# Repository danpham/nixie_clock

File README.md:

# Nixie Clock ESP32-C3

A **Nixie tube clock project** based on the **ESP32-C3**, using **IN14** and **IN3** tubes driven by **HV5622** high-voltage drivers.

## Hardware

- **Microcontroller:** ESP32-C3  
- **Nixie tubes:** 6 × IN14 and 2 × IN3  
- **Driver:** HV5622 for cathode switching  
- **Rotary encoder:** EC11 for time configuration  
- **3.3V regulator:** AP63203WU to power the ESP32-C3 and logic components  
- **PCB design:** SMD (Surface-Mount) components

> [!WARNING]
> This project involves high voltage. Follow proper electrical safety procedures!

## Current Features

- Nixie tube display control via HV5622
- Rotary encoder input (EC11) for setting the time
- Internal clock management
- **Anti–cathode poisoning routine:** periodic cycling and cathode management to prevent oxide buildup and extend tube lifespan
- Wi-Fi connectivity with NTP time synchronization
- Web interface for configuration

## Future Features

- Web interface for configuration: timezone, brightness, night mode, and display enable/disable

## Software

The code is written in **C for the ESP32-C3**, organized as follows:

```
software/nixie_clock_esp32_project/
├── components/
│   ├── uart/
│   ├── gpio_driver/
│   ├── display/
│   ├── clock/
│   ├── hv5622/
│   ├── rotary_encoder/
│   └── wifi/
└── main/
```

### Code Quality & Standards

- The firmware is developed in compliance with MISRA C:2012 guidelines to ensure reliability and safety in embedded systems.
- Modular driver-based architecture for maintainability and scalability.

## Usage

### Wi-Fi Configuration

To connect to the Nixie clock, use the following credentials:

```c
WIFI_SSID     "NixieClock-Setup"
WIFI_PASSWORD "12345678"
```

### Compilation

The project uses **ESP-IDF for ESP32-C3**. Make sure your ESP32-C3 development environment is properly set up.

```bash
cd software/nixie_clock_esp32_project
idf.py build
idf.py flash
```

## Test

### Unit testing

In ESP-IDF terminal:
```bash
cd software/nixie_clock_esp32_project/test/unit
cmake -S . -B build
cmake --build build --config Release
.\build\Release\native_tests.exe
```

### Integration testing

In ESP-IDF terminal:
```bash
cd software/nixie_clock_esp32_project/test/integration
cmake -S . -B build
cmake --build build --config Release
.\build\Release\native_integration_tests.exe
```

## Documentation

The generated documentation for this project is available [here](https://danpham.github.io/nixie_clock/).

## License

This project is released under the **LGPL v3** license.
A separate `LICENSE` file contains the complete text of the license.

## Safety

> [!WARNING]
> This project involves **high voltage (~170V for Nixie tubes)**.

- Never touch the circuit while it is powered
- Work carefully and only with proper knowledge of high-voltage electronics

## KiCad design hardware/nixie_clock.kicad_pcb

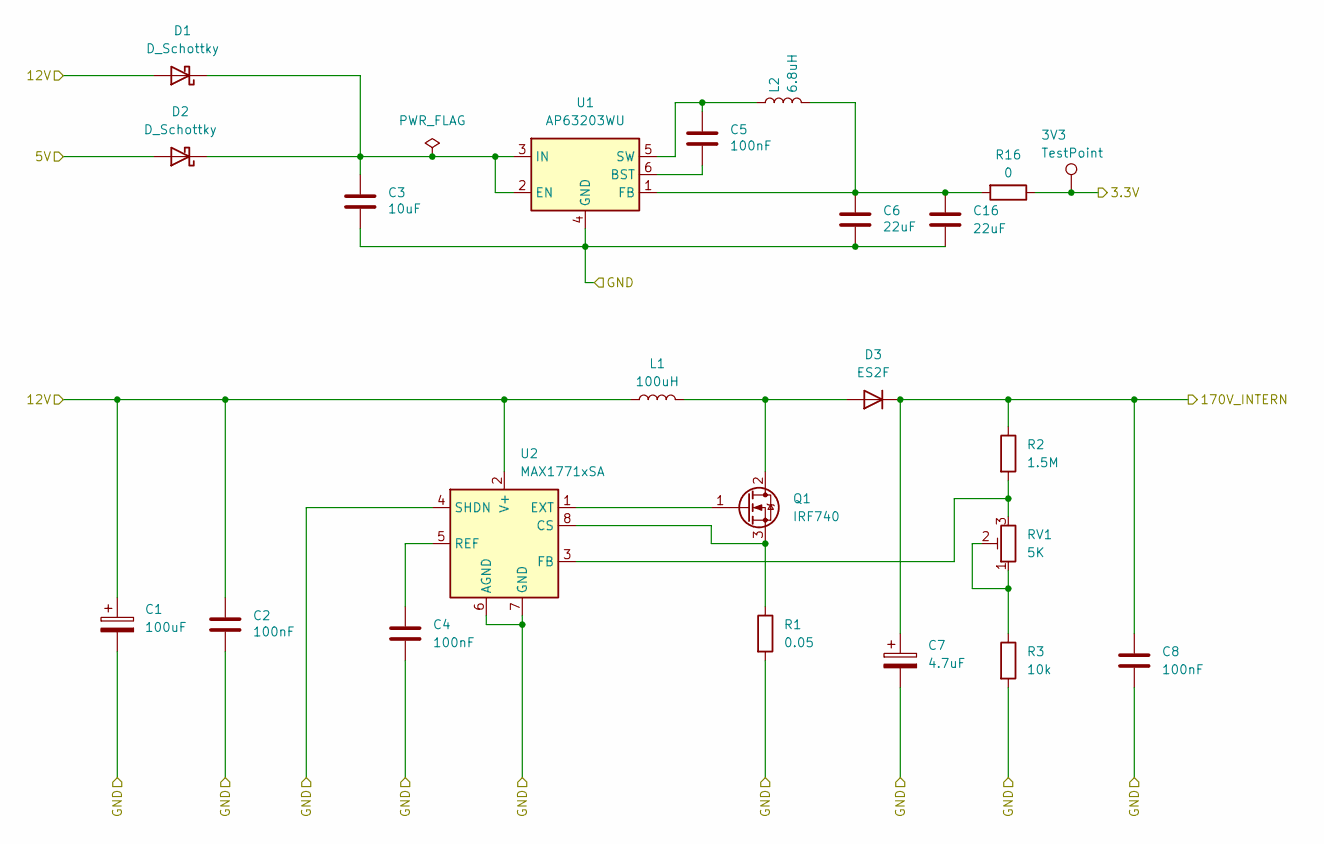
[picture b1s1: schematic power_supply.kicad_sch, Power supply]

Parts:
3V3: TestPoint; TestPoint_Pad_D1.5mm
C1: 100uF; CP_EIA-7343-31_Kemet-D_HandSolder
C2, C4, C5: 100nF; C_0805_2012Metric
C3: 10uF; C_1206_3216Metric
C6, C16: 22uF; C_1206_3216Metric
C7: 4.7uF; C_Elec_8x10.2
C8: 100nF; C_1210_3225Metric_Pad1.33x2.70mm_HandSolder
D1, D2: D_Schottky; D_SMB
D3: ES2F; D_SMB
L1: 100uH; L_APV_APH1050
L2: 6.8uH; L_Bourns_SRN8040TA
Q1: IRF740; TO-263-2
R1: 0.05; R_0805_2012Metric
R2: 1.5M; R_0805_2012Metric
R3: 10k; R_0805_2012Metric
R16: 0; R_1206_3216Metric
RV1: 5K; Potentiometer_Bourns_3314J_Vertical
U1: AP63203WU; TSOT-23-6
U2: MAX1771xSA; SO-8_3.9x4.9mm_P1.27mm

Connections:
/connectors/5V: D2.2 (A); also elsewhere on the board
/connectors/12V: C1.1, C2.1, D1.2 (A), L1.1, U2.2 (V+); also elsewhere on the board
/connectors/GND: C1.2, C2.2, C3.2, C4.2, C6.2, C7.2, C8.2, C16.2, R1.2, R3.2, U1.4 (GND), U2.4 (SHDN), U2.6 (AGND), U2.7 (GND); also elsewhere on the board
/cpu/3.3V: 3V3.1, R16.1; also elsewhere on the board
/driver_3_digits_1_dot_left/170V_INTERN: C7.1, C8.1, D3.1 (K), R2.1; also elsewhere on the board
unnamed: C3.1, D1.1 (K), D2.1 (K), U1.2 (EN), U1.3 (IN)
unnamed: D3.2 (A), L1.2, Q1.2 (D)
unnamed: Q1.1 (G), U2.1 (EXT)
unnamed: Q1.3 (S), R1.1, U2.8 (CS)
unnamed: R3.1, RV1.1, RV1.2
unnamed: C5.2, U1.6 (BST)
unnamed: C6.1, C16.1, L2.2, R16.2, U1.1 (FB)
unnamed: C5.1, L2.1, U1.5 (SW)
unnamed: R2.2, RV1.3, U2.3 (FB)
unnamed: C4.1, U2.5 (REF)

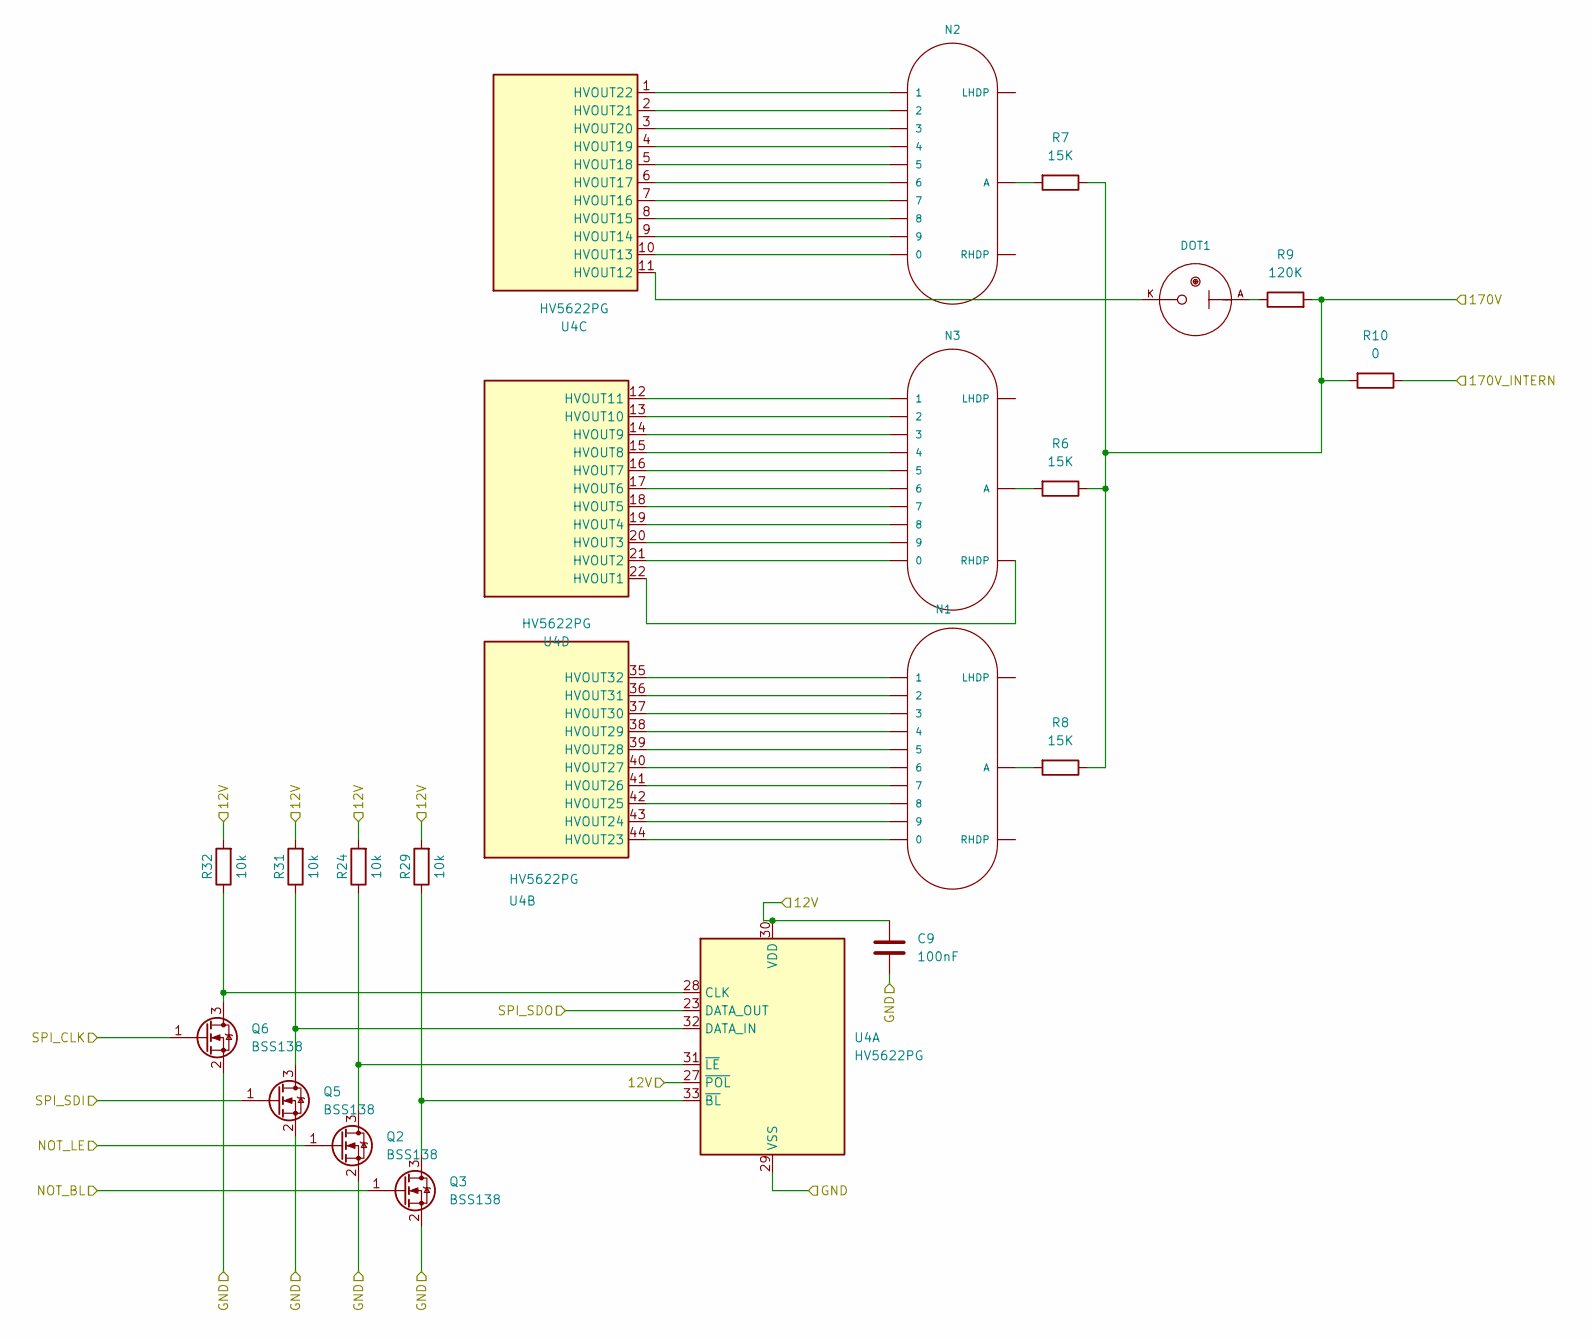
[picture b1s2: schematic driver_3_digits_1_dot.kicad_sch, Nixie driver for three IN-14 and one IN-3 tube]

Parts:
C9: 100nF; R_0805_2012Metric
DOT1: IN-3; nixies-us-IN-3
N1, N2, N3: IN-14; nixies-us-IN-14
Q2, Q3, Q5, Q6: BSS138; SOT-23
R6, R7, R8: 15K; R_1206_3216Metric
R9: 120K; R_1206_3216Metric
R10: 0; R_1206_3216Metric
R24, R29, R31, R32: 10k; R_0805_2012Metric
U4: HV5622PG; PQFP-44_10x10mm_P0.8mm

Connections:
/connectors/12V: C9.2, R24.2, R29.2, R31.2, R32.2, U4.27 (~POL), U4.30 (VDD); also elsewhere on the board
/connectors/170V: R6.1, R7.1, R8.1, R9.2, R10.2; also elsewhere on the board
/connectors/GND: C9.1, Q2.2 (S), Q3.2 (S), Q5.2 (S), Q6.2 (S), U4.29 (VSS); also elsewhere on the board
/cpu/GPIO1: Q3.1 (G); also elsewhere on the board
/cpu/GPIO2: Q2.1 (G); also elsewhere on the board
/cpu/SPI_CLK: Q6.1 (G); also elsewhere on the board
/cpu/SPI_MOSI: Q5.1 (G); also elsewhere on the board
/driver_3_digits_1_dot_left/170V_INTERN: R10.1; also elsewhere on the board
/driver_3_digits_1_dot_left/SPI_SDO: U4.23 (DATA_OUT); also elsewhere on the board
unnamed: DOT1.A, R9.1
unnamed: N1.A, R8.2
unnamed: N2.A, R7.2
unnamed: N3.A, R6.2
unnamed: Q2.3 (D), R24.1, U4.31 (~LE)
unnamed: Q3.3 (D), R29.1, U4.33 (~BL)
unnamed: Q5.3 (D), R31.1, U4.32 (DATA_IN)
unnamed: Q6.3 (D), R32.1, U4.28 (CLK)
unnamed: N1.0, U4.44 (HVOUT23)
unnamed: N1.9, U4.43 (HVOUT24)
unnamed: N1.8, U4.42 (HVOUT25)
unnamed: N1.7, U4.41 (HVOUT26)
unnamed: N1.6, U4.40 (HVOUT27)
unnamed: N1.5, U4.39 (HVOUT28)
unnamed: N1.4, U4.38 (HVOUT29)
unnamed: N1.3, U4.37 (HVOUT30)
unnamed: N1.2, U4.36 (HVOUT31)
unnamed: N1.1, U4.35 (HVOUT32)
unnamed: DOT1.K, U4.11 (HVOUT12)
unnamed: N2.0, U4.10 (HVOUT13)
unnamed: N2.9, U4.9 (HVOUT14)
unnamed: N2.8, U4.8 (HVOUT15)
unnamed: N2.7, U4.7 (HVOUT16)
unnamed: N2.6, U4.6 (HVOUT17)
unnamed: N2.5, U4.5 (HVOUT18)
unnamed: N2.4, U4.4 (HVOUT19)
unnamed: N2.3, U4.3 (HVOUT20)
unnamed: N2.2, U4.2 (HVOUT21)
unnamed: N2.1, U4.1 (HVOUT22)
unnamed: N3.RHDP, U4.22 (HVOUT1)
unnamed: N3.0, U4.21 (HVOUT2)
unnamed: N3.9, U4.20 (HVOUT3)
unnamed: N3.8, U4.19 (HVOUT4)
unnamed: N3.7, U4.18 (HVOUT5)
unnamed: N3.6, U4.17 (HVOUT6)
unnamed: N3.5, U4.16 (HVOUT7)
unnamed: N3.4, U4.15 (HVOUT8)
unnamed: N3.3, U4.14 (HVOUT9)
unnamed: N3.2, U4.13 (HVOUT10)
unnamed: N3.1, U4.12 (HVOUT11)

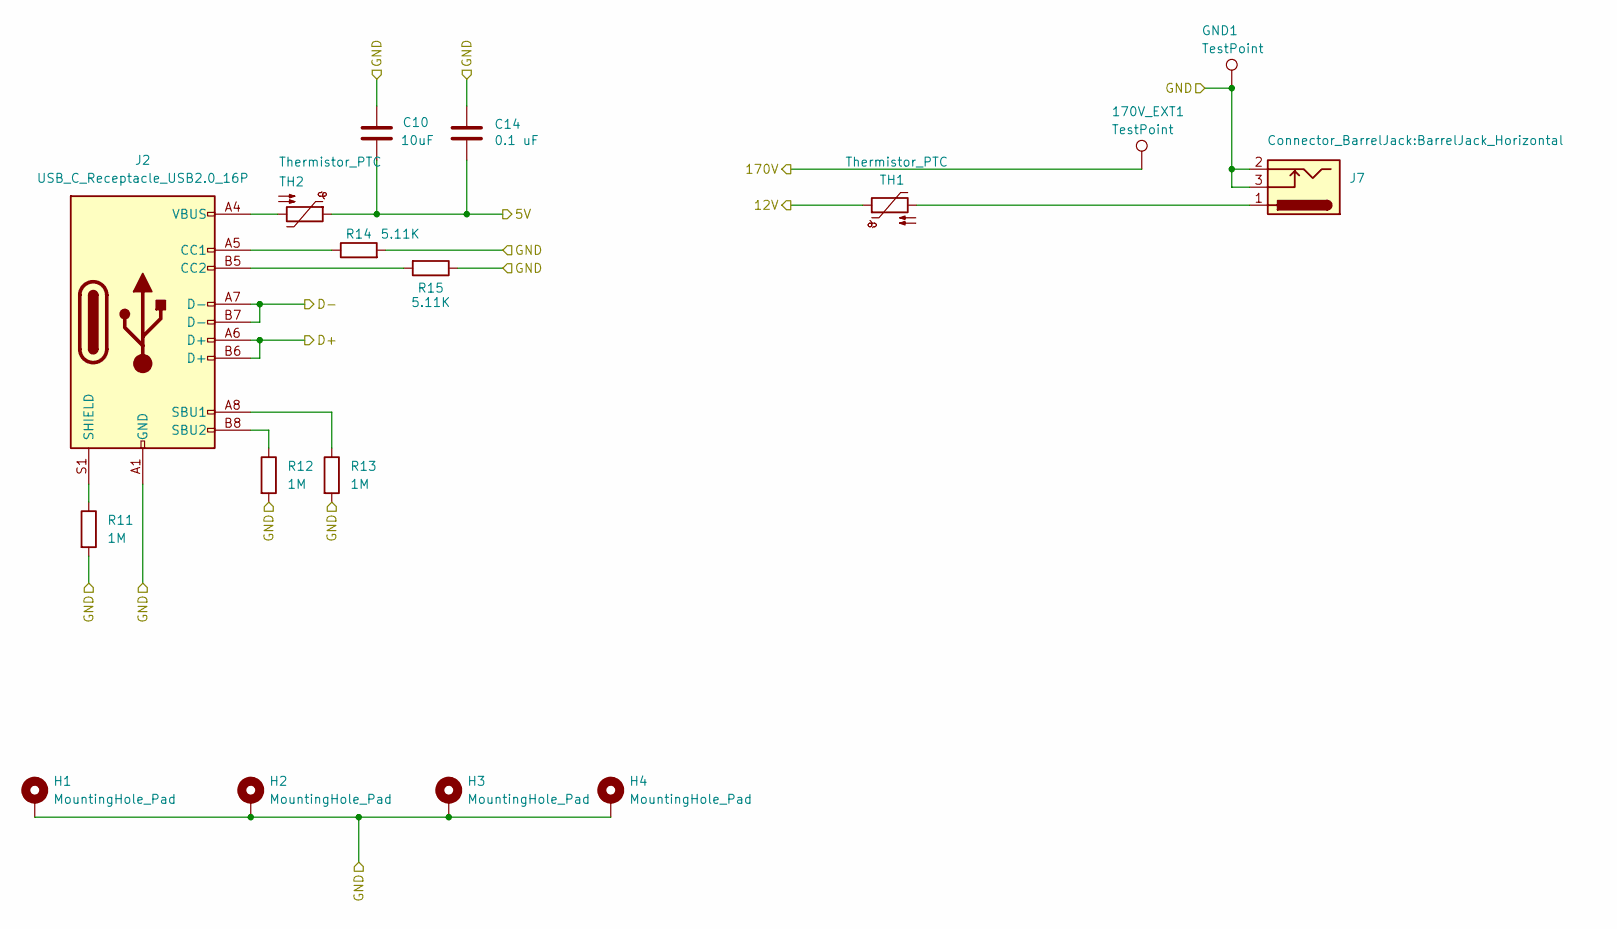
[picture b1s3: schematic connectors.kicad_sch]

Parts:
170V_EXT1: TestPoint; TestPoint_Pad_D1.5mm
C10: 10uF; C_1206_3216Metric
C14: 0.1 uF; C_0805_2012Metric
GND1: TestPoint; TestPoint_Pad_D1.5mm
H1, H2, H3, H4: MountingHole_Pad; MountingHole_3.2mm_M3_Pad_Via
J2: USB_C_Receptacle_USB2.0_16P; USB_C_Receptacle_GCT_USB4105-xx-A_16P_TopMnt_Horizontal
J7: Barrel_Jack_Switch; BarrelJack_Horizontal
R11, R12, R13: 1M; R_1206_3216Metric
R14, R15: 5.11K; R_1206_3216Metric
TH1, TH2: Thermistor_PTC; R_1206_3216Metric

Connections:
/connectors/5V: C10.2, C14.2, TH2.1; also elsewhere on the board
/connectors/12V: TH1.1; also elsewhere on the board
/connectors/170V: 170V_EXT1.1; also elsewhere on the board
/connectors/D+: J2.A6 (D+), J2.B6 (D+); also elsewhere on the board
/connectors/D-: J2.A7 (D-), J2.B7 (D-); also elsewhere on the board
/connectors/GND: C10.1, C14.1, GND1.1, H1.1, H2.1, H3.1, H4.1, J2.A1 (GND), J2.A12 (GND), J2.B1 (GND), J2.B12 (GND), J7.2, J7.3, R11.2, R12.2, R13.2, R14.2, R15.1; also elsewhere on the board
unnamed: J2.A5 (CC1), R14.1
unnamed: J2.B5 (CC2), R15.2
unnamed: J2.A8 (SBU1), R13.1
unnamed: J2.B8 (SBU2), R12.1
unnamed: J2.S1 (SHIELD), R11.1
unnamed: J2.A4 (VBUS), J2.A9 (VBUS), J2.B4 (VBUS), J2.B9 (VBUS), TH2.2
unnamed: J7.1, TH1.2

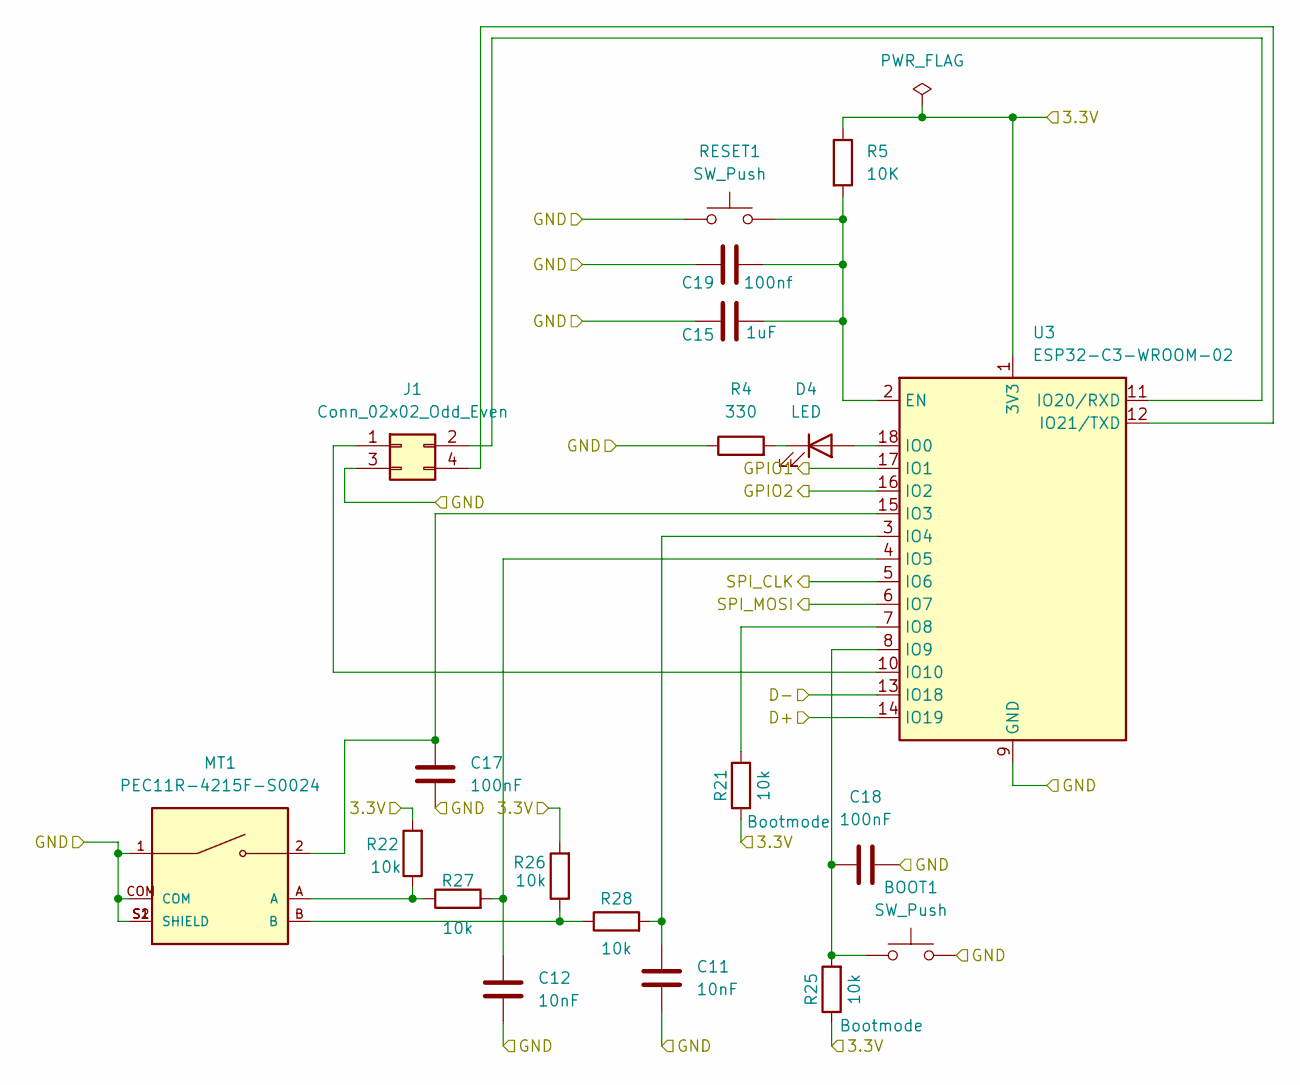
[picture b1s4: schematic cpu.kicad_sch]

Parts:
BOOT1: SW_Push; SW_SPST_Omron_B3FS-100xP
C11, C12: 10nF; R_0805_2012Metric
C15: 1uF; R_0805_2012Metric
C17, C18: 100nF; R_0805_2012Metric
C19: 100nf; R_0805_2012Metric
D4: LED; LED_0805_2012Metric
J1: Conn_02x02_Odd_Even; PinHeader_2x02_P2.54mm_Vertical_SMD
MT1: PEC11R-4215F-S0024; XDCR_PEC11R-4215F-S0024; PARTREV Rev. 09/19
R4: 330; R_0805_2012Metric
R5: 10K; R_0805_2012Metric
R21, R22, R25, R26, R27, R28: 10k; R_0805_2012Metric
RESET1: SW_Push; SW_SPST_Omron_B3FS-100xP
U3: ESP32-C3-WROOM-02

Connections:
/connectors/D+: U3.14 (IO19); also elsewhere on the board
/connectors/D-: U3.13 (IO18); also elsewhere on the board
/connectors/GND: BOOT1.2, C11.2, C12.2, C15.1, C17.2, C18.2, C19.1, J1.3, MT1.1, MT1.COM, MT1.S1 (SHIELD), MT1.S2 (SHIELD), R4.1, RESET1.1, U3.9 (GND), U3.19 (GND); also elsewhere on the board
/cpu/3.3V: R5.1, R21.1, R22.2, R25.1, R26.2, U3.1 (3V3); also elsewhere on the board
/cpu/GPIO1: U3.17 (IO1); also elsewhere on the board
/cpu/GPIO2: U3.16 (IO2); also elsewhere on the board
/cpu/SPI_CLK: U3.5 (IO6); also elsewhere on the board
/cpu/SPI_MOSI: U3.6 (IO7); also elsewhere on the board
unnamed: D4.2 (A), U3.18 (IO0)
unnamed: D4.1 (K), R4.2
unnamed: J1.1, U3.10 (IO10)
unnamed: J1.2, U3.11 (IO20/RXD)
unnamed: J1.4, U3.12 (IO21/TXD)
unnamed: MT1.A, R22.1, R27.1
unnamed: MT1.B, R26.1, R28.1
unnamed: C15.2, C19.2, R5.2, RESET1.2, U3.2 (EN)
unnamed: C17.1, MT1.2, U3.15 (IO3)
unnamed: C11.1, R28.2, U3.3 (IO4)
unnamed: C12.1, R27.2, U3.4 (IO5)
unnamed: R21.2, U3.7 (IO8)
unnamed: BOOT1.1, C18.1, R25.2, U3.8 (IO9)

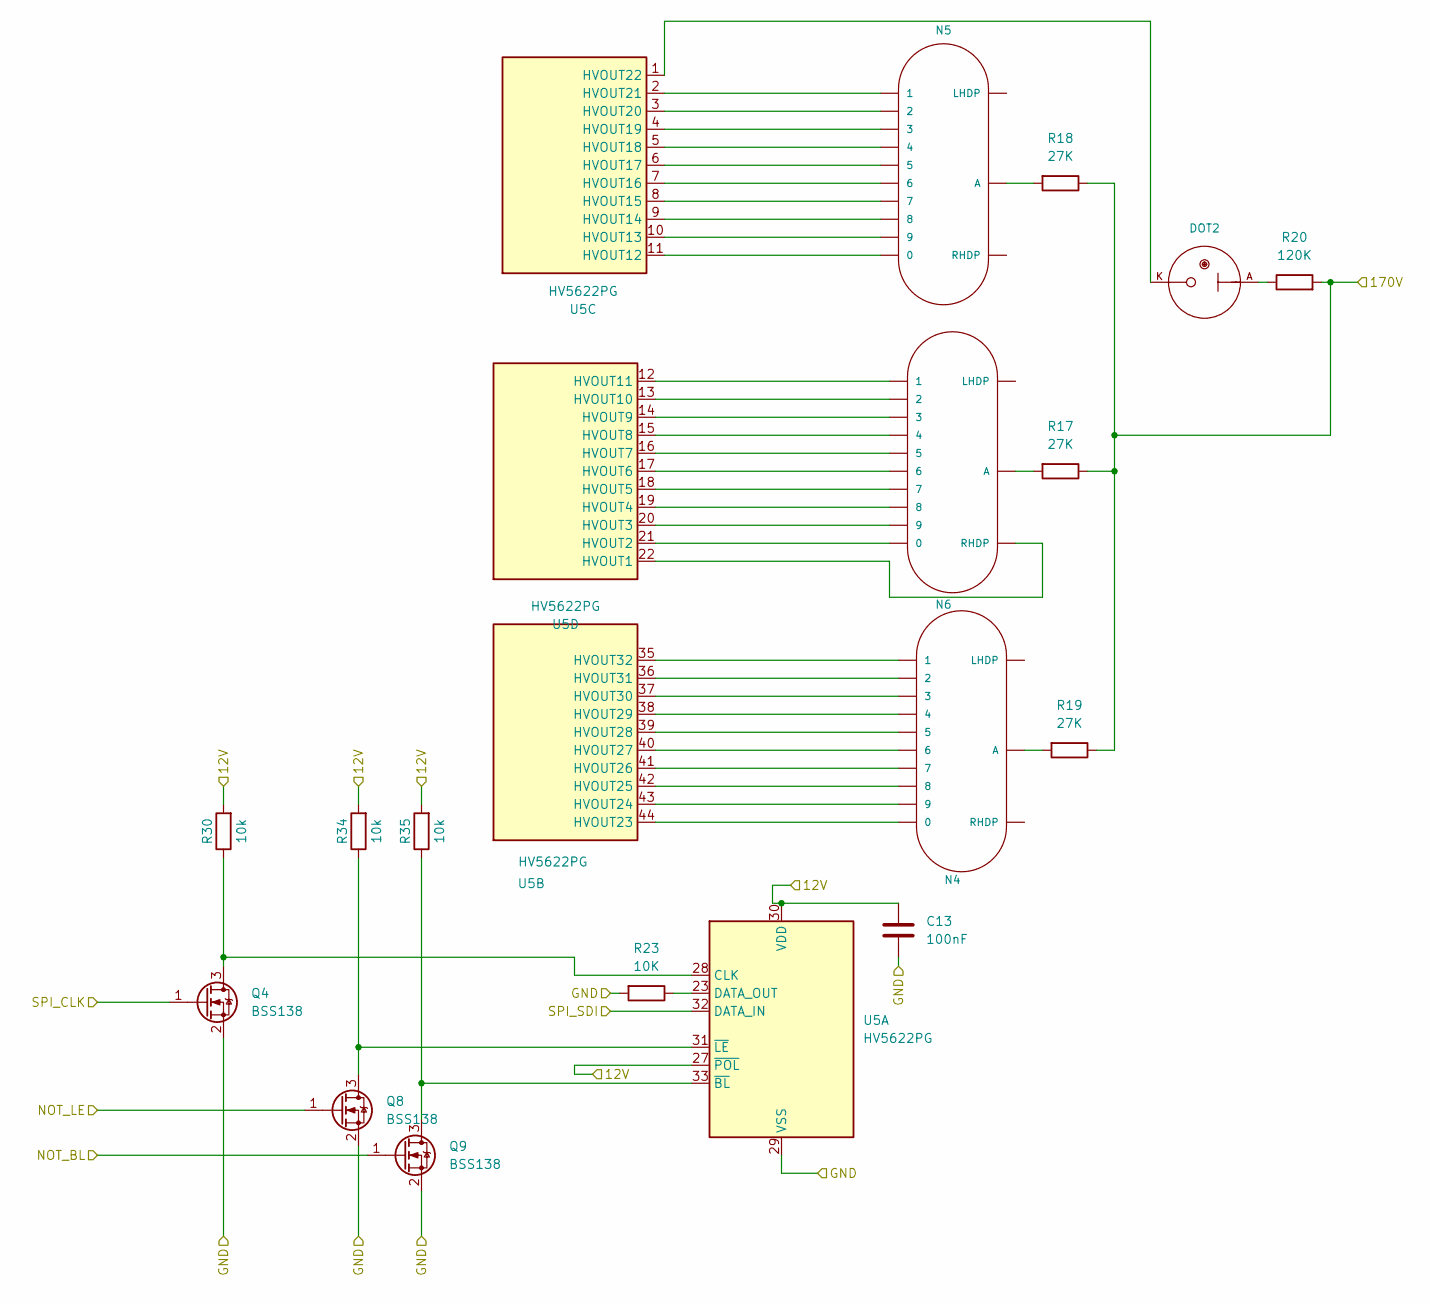
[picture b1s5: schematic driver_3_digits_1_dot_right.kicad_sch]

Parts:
C13: 100nF; R_0805_2012Metric
DOT2: IN-3; nixies-us-IN-3
N4, N5, N6: IN-14; nixies-us-IN-14
Q4, Q8, Q9: BSS138; SOT-23
R17, R18, R19: 27K; R_1206_3216Metric
R20: 120K; R_1206_3216Metric
R23: 10K; R_0805_2012Metric
R30, R34, R35: 10k; R_0805_2012Metric
U5: HV5622PG; PQFP-44_10x10mm_P0.8mm

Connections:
/connectors/12V: C13.2, R30.2, R34.2, R35.2, U5.27 (~POL), U5.30 (VDD); also elsewhere on the board
/connectors/170V: R17.1, R18.1, R19.1, R20.2; also elsewhere on the board
/connectors/GND: C13.1, Q4.2 (S), Q8.2 (S), Q9.2 (S), R23.2, U5.29 (VSS); also elsewhere on the board
/cpu/GPIO1: Q9.1 (G); also elsewhere on the board
/cpu/GPIO2: Q8.1 (G); also elsewhere on the board
/cpu/SPI_CLK: Q4.1 (G); also elsewhere on the board
/driver_3_digits_1_dot_left/SPI_SDO: U5.32 (DATA_IN); also elsewhere on the board
unnamed: DOT2.A, R20.1
unnamed: N4.A, R19.2
unnamed: N5.A, R18.2
unnamed: N6.A, R17.2
unnamed: Q4.3 (D), R30.1, U5.28 (CLK)
unnamed: Q8.3 (D), R34.1, U5.31 (~LE)
unnamed: Q9.3 (D), R35.1, U5.33 (~BL)
unnamed: R23.1, U5.23 (DATA_OUT)
unnamed: N4.0, U5.44 (HVOUT23)
unnamed: N4.9, U5.43 (HVOUT24)
unnamed: N4.8, U5.42 (HVOUT25)
unnamed: N4.7, U5.41 (HVOUT26)
unnamed: N4.6, U5.40 (HVOUT27)
unnamed: N4.5, U5.39 (HVOUT28)
unnamed: N4.4, U5.38 (HVOUT29)
unnamed: N4.3, U5.37 (HVOUT30)
unnamed: N4.2, U5.36 (HVOUT31)
unnamed: N4.1, U5.35 (HVOUT32)
unnamed: N5.0, U5.11 (HVOUT12)
unnamed: N5.9, U5.10 (HVOUT13)
unnamed: N5.8, U5.9 (HVOUT14)
unnamed: N5.7, U5.8 (HVOUT15)
unnamed: N5.6, U5.7 (HVOUT16)
unnamed: N5.5, U5.6 (HVOUT17)
unnamed: N5.4, U5.5 (HVOUT18)
unnamed: N5.3, U5.4 (HVOUT19)
unnamed: N5.2, U5.3 (HVOUT20)
unnamed: N5.1, U5.2 (HVOUT21)
unnamed: DOT2.K, U5.1 (HVOUT22)
unnamed: N6.RHDP, U5.22 (HVOUT1)
unnamed: N6.0, U5.21 (HVOUT2)
unnamed: N6.9, U5.20 (HVOUT3)
unnamed: N6.8, U5.19 (HVOUT4)
unnamed: N6.7, U5.18 (HVOUT5)
unnamed: N6.6, U5.17 (HVOUT6)
unnamed: N6.5, U5.16 (HVOUT7)
unnamed: N6.4, U5.15 (HVOUT8)
unnamed: N6.3, U5.14 (HVOUT9)
unnamed: N6.2, U5.13 (HVOUT10)
unnamed: N6.1, U5.12 (HVOUT11)

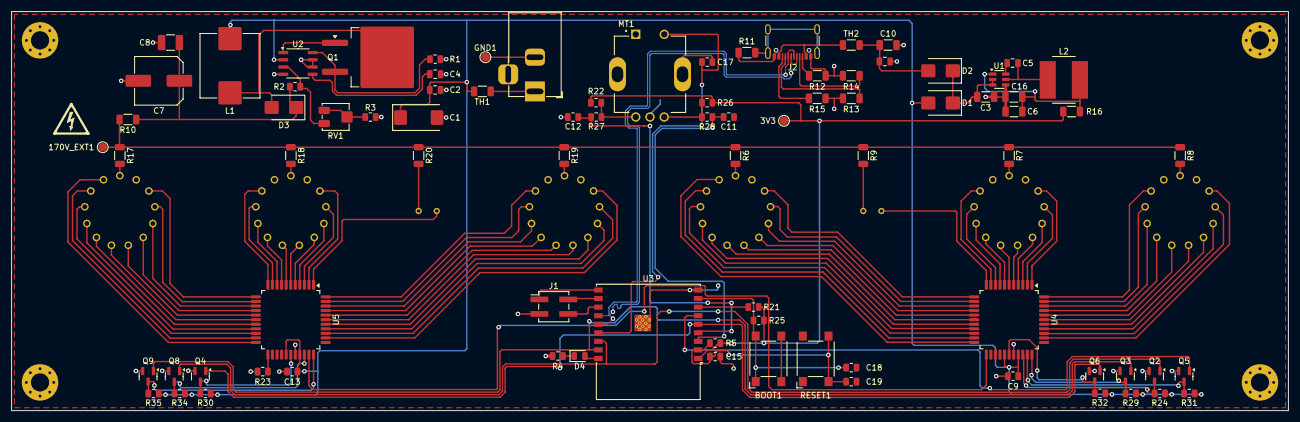
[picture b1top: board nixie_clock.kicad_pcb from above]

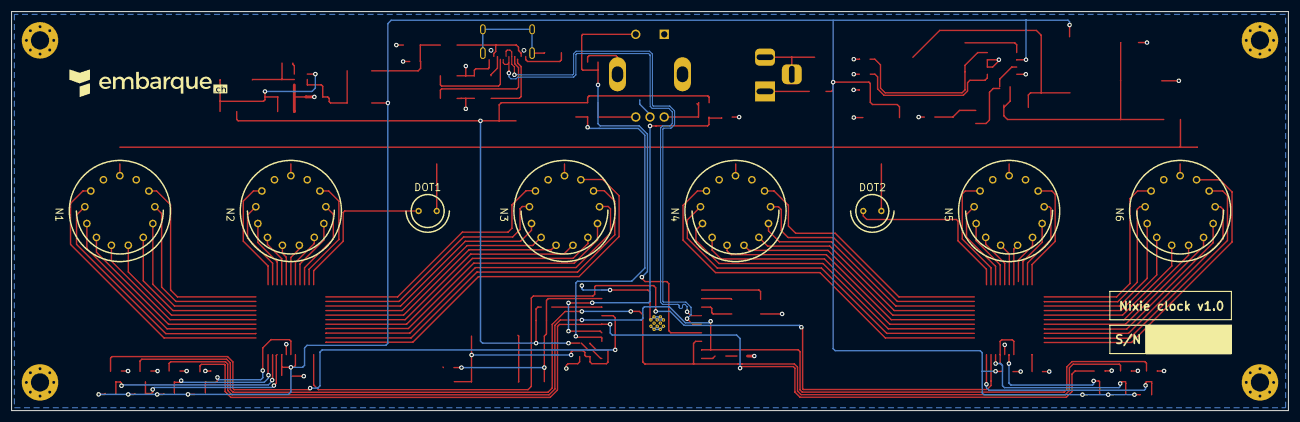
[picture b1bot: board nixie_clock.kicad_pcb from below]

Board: 2 copper layers, 224.0 x 70.0 mm, 96 parts (8 on the bottom side), 123 nets.

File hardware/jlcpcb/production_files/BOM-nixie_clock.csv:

Comment,Designator,Footprint,LCSC,Quantity
Barrel_Jack_Switch,J7,BarrelJack_Horizontal,C111567,1
1.5M,R2,R_0805_2012Metric,C118025,1
100uF,C1,CP_EIA-7343-31_Kemet-D_HandSolder,C122302,1
100nF,"C13,C9",R_0805_2012Metric,C126469,2
22uF,"C16,C6",C_1206_3216Metric,C12891,2
10uF,"C10,C3",C_1206_3216Metric,C13585,2
PEC11R-4215F-S0024,MT1,XDCR_PEC11R-4215F-S0024,C143790,1
ES2F,D3,D_SMB,C145321,1
15K,"R6,R7,R8",R_1206_3216Metric,C1493,3
10nF,"C11,C12",R_0805_2012Metric,C1589,2
10k,"R21,R22,R23,R24,R25,R26,R27,R28,R29,R30,R31,R32,R34,R35,R5",R_0805_2012Metric,C17414,15
330,R4,R_0805_2012Metric,C17630,1
0,"R10,R16",R_1206_3216Metric,C17888,2
120K,"R20,R9",R_1206_3216Metric,C17908,2
1M,"R11,R12,R13",R_1206_3216Metric,C17927,3
27K,"R17,R18,R19",R_1206_3216Metric,C17943,3
HV5622PG,"U4,U5",PQFP-44_10x10mm_P0.8mm,C220637,2
0.05,R1,R_0805_2012Metric,C247602,1
D_Schottky,D2,D_SMB,C2479,1
D_Schottky,D1,D_SMB,C2480,1
10k,R3,R_0805_2012Metric,C269724,1
1uF,C15,R_0805_2012Metric,C28323,1
6.8uH,L2,L_Bourns_SRN8040TA,C2849553,1
USB_C_Receptacle_USB2.0_16P,J2,USB_C_Receptacle_GCT_USB4105-xx-A_16P_TopMnt_Horizontal,C2894897,1
ESP32-C3-WROOM-02,U3,ESP32-C3-WROOM-02,C2934560,1
100uH,L1,L_APV_APH1050,C2962892,1
IRF740,Q1,TO-263-2,C39238,1
0.1 uF,"C14,C17,C18,C19,C2,C4,C5",C_0805_2012Metric,C396718,7
MAX1771xSA,U2,SO-8_3.9x4.9mm_P1.27mm,C407903,1
100nF,C8,C_1210_3225Metric_Pad1.33x2.70mm_HandSolder,C52020,1
BSS138,"Q2,Q3,Q4,Q5,Q6,Q8,Q9",SOT-23,C52895,7
Thermistor_PTC,TH1,R_1206_3216Metric,C5678440,1
5K,RV1,Potentiometer_Bourns_3314J_Vertical,C58391,1
AP63203WU,U1,TSOT-23-6,C780769,1
SW_Push,"BOOT1,RESET1",SW_SPST_Omron_B3FS-100xP,C87038,2
5.11K,"R14,R15",R_1206_3216Metric,C870811,2
Thermistor_PTC,TH2,R_1206_3216Metric,C883122,1
4.7uF,C7,C_Elec_8x10.2,C88702,1
Conn_02x02_Odd_Even,J1,PinHeader_2x02_P2.54mm_Vertical_SMD,C919361,1
LED,D4,LED_0805_2012Metric,C965812,1
TestPoint,GND1,TestPoint_Pad_D1.5mm,,1
TestPoint,3V3,TestPoint_Pad_D1.5mm,,1
IN-14,N6,nixies-us-IN-14,,1
IN-3,DOT1,nixies-us-IN-3,,1
IN-14,N3,nixies-us-IN-14,,1
IN-3,DOT2,nixies-us-IN-3,,1
IN-14,N1,nixies-us-IN-14,,1
IN-14,N4,nixies-us-IN-14,,1
IN-14,N5,nixies-us-IN-14,,1
IN-14,N2,nixies-us-IN-14,,1
TestPoint,170V_EXT1,TestPoint_Pad_D1.5mm,,1

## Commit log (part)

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2025-06-17 Initial commit.
2025-06-19 Update.
2025-06-21 First routage.
2025-06-22 Update vias.
2025-06-23 Add buttons.
2025-06-23 Add HT psu.
2025-06-26 Add holes with via. Avoid too long tracks.
2025-07-06 Change power connector.
2025-08-17 Rework some tracks.
2025-08-17 Fix USB lane size.
2025-08-17 Fix DRC errors.
2025-08-18 Add clearance of 0.8mm on HV lines for every nixie tube.
2025-08-18 Add space arround C13.
2025-08-18 Rework C9. Placed closer to the power pad.
2025-08-18 Tweaks.
2025-08-20 Add sources of test software.
2025-08-20 Remove POLarity setup, needs 12V to be not reversed.
2025-08-20 Fix DRC erros.
2025-08-21 C15, C13, C9 changed to 805 form factor. Removed tracks under capacitors.
2025-08-21 Fix tube resistors and capacitors with 805.
2025-08-23 Rework 3.3v power supply (fix error on fb loop). Put 1206 back on HV part.
2025-08-24 Fix most of ERC on schema. Add missing wire on RV1. Add PWR_FLG on GND to avoid error. Add resistor for unused SPI_OUT of HV5622. Add PTC on 3v3 supply.
2025-08-25 Add pull down resistors for non used pins.
2025-08-25 Remove DRC error.
2025-08-25 Add serial on silkscren.
2025-08-25 Tweak USB.
2025-08-27 Add button handling.
2025-08-27 Update PCB.
2025-08-27 Add pinout mapping. Update display software.
2025-08-28 Fix error.
2025-08-28 Add unit tests.
2025-08-28 Add clock unit tests.
2025-08-28 Update 2 vias. Update settings.json.
2025-08-28 Add mock for hv5622.
2025-08-28 Add integration tests. Add toggling of the dots each second.
2025-08-28 Mock files for hv5622.
2025-08-29 Replace input with 12V barrel connector. Add test point for alternative 170V input.
2025-08-30 Center USB-C connector on PCB. Add testpoints.
2025-09-04 Add anti-poisonning routine. Add test for this routine.
2025-09-04 Add embarque logo as library.
2025-09-04 Remove .dxf file, useless.
2025-09-05 Update components to match BOM.
2025-09-06 Add dot ch logo.
2025-09-30 Limitate inrush current (decoupling capacitors after PTCs). Add decoupling capacitors for VUSB.
2025-09-30 Revert GND layer to original position.
2025-09-30 Update, DRC ok.
2025-09-30 Add 3314J potentiometer. Found L2 LCSC part number.
2025-10-10 Add PEC11 encoder instead of pushbuttons switches.
2025-10-10 Change to path on 3V3 Testpoint.
2025-10-10 Rework track.
2025-10-10 Add capacitor for rotary switch.
2025-10-12 Add IO1 to pin header. Add .step models.
2025-10-12 Add rotary encoder.
2025-10-12 Add MISRA C checks on workflow.
2025-10-12 Add via stitching.
2025-10-12 Update components paths for Misra checks.
2025-10-12 Update components paths for Misra checks. Fix Misra errors.
2025-10-12 MISRA fix 2.
2025-10-12 Remove unused pattern_loops variable.
2025-10-12 MISRA fix 3.
2025-10-12 MISRA fix 4.
2025-10-12 MISRA fix 6. Add UART output.
2025-10-12 MISRA fix 7.
2025-10-12 MISRA fix 8.
2025-10-12 MISRA fix 7.MISRA fix 9.
2025-10-12 MISRA fix 10.
2025-10-12 MISRA fix 11.
2025-10-12 Add docs. Add .gitignore.
2025-10-12 Update doc tree.
2025-10-14 Remove useless 10k resistor for PEC11 switch.
2025-10-15 Add BOOT1 and RESET1 buttons. Add pullups on Boot strapping pins GPIO8,9. Fix EN, enable input.
2025-10-15 Add pictures.
2025-10-15 Add images to README for project visualization
    Added images of the 3D view and PCB view to README.
2025-10-15 Update README to remove duplicate image
    Removed duplicate PCB view image and adjusted formatting.
2025-10-16 Removed useless vias.
2025-10-16 Remap /LE and /BL to GPIO2 and GPIO1. SPI2 clk to GPIO6, SPI2 data to GPIO7.
2025-10-16 Update SPI2 config.
2025-10-16 Add high voltage symbol.
2025-10-16 Add modified HV symbol.
2025-10-16 Use PCB cleanup tool from Kicad.
2025-10-17 Add mosfets for handling levels.
2025-10-17 Route conversion level mosfets.
2025-10-17 Cleanup vias and tracks.
2025-10-17 Rework text positions.
2025-10-17 Remove one mosfet on the right since SPI out from the first HV5622 is already on 12v level.
2025-10-18 Remove one via near HV5622. Tweaks.
2025-10-18 Put R23 horizontaly.
2025-10-18 Remove one unused track.
2025-10-18 Update README.
2025-10-18 Modify code to invert data due to mosfets.
2025-10-18 Simplify 12V rail on U5.
2025-10-18 Increase text size for Nixies and dots silkscreen. Fix solder mask opening error on JLPCB DFM. Correct one warning distance to pad on mosfets.
2025-10-18 Correct N3 placement.
2025-10-21 Add testing instructions to README
    Added sections for unit and integration testing instructions.
2025-10-21 Update README with testing instructions
    Added instructions for unit and integration testing in ESP-IDF.
2025-10-21 Add rotary encoder unit tests.
2025-10-22 Add quadrature support for rotary encoder. Update rotary encoder unit test.
2025-11-01 Fix tests after Misra changes. Correct a regression in rotary_encoder.c.
2025-11-01 Remove clock_set, use a modified version of clock_init instead.
2025-11-01 Remove clock_set in unit tests.
2025-11-01 Add NTP time synchronization with Wifi.
2025-11-01 Fix MISRA.
2025-11-02 Use callback for NTP sync, every 30mins.
2025-11-02 no message
2025-11-02 Improve code size.
2025-11-02 Update BOM.
2025-11-07 Update R14, R15 LCSC reference for availability.
2025-11-08 Add Webserver for config page. Add NVS management. Add Config. Modify Wifi for AP and STA mode.
2025-11-09 Misra fix.
2025-11-13 Make config_init thread safe.
2025-11-13 Fix unit test clock.
2025-11-14 Add wifi_change_sta() to update STA connection avec SSID/passphrase update.
2025-11-14 Use wifi_change_sta().
2025-11-14 NTP and wifi update are working.
2025-11-14 Rename nvs_load_counter.
2025-11-15 Rework ntp_sync_task with binary semaphore.
2025-11-15 Add nvs unit tests.
2025-11-15 Improve presentation on nvs tests.
2025-11-15 Clean up useless headers.
2025-11-15 Move ntp_sync_task to ntp component.
2025-11-15 Write time with webserver.
2025-11-16 Add clockUpdarteQueue.
2025-11-16 Enhance README with web interface and usage info
    Updated README to include web interface details and usage instructions.
2025-11-16 Add queue checks. Update html.
2025-11-16 Fix error, event was not received.
2025-11-16 Ai audit.
2025-11-17 Try to simplify html page format.
2025-11-17 Add mode feature. Simplify clock_menu fonction.
2025-11-18 Add UML architecture.
2025-11-18 Update architecture.
2025-11-18 Add PWM control (Brightness control).
2025-11-19 Add service manager to fit new sw architecture.
2025-11-20 Generate doc.
2025-11-20 deploy: 4a66b84801d7317ab924e5fc9d61f926f4e34987
2025-11-20 For graphs.
2025-11-20 deploy: 21f91bff8bf167e53e45ff159a35ee342364bb8b
2025-11-20 Add documentation section to README
    Added a section for project documentation with a link.
2025-11-20 Remove doc warnings.
2025-11-20 deploy: a70a872072c39b5a72bd245978c1855e8ab32401
2025-11-20 Doc images in svg format.
2025-11-20 Update doc.
2025-11-20 deploy: 1dd983d26235a689410f17da5ef07f8be1fb0f73
2025-11-20 No latex, no xml output for doc.
2025-11-22 Switch to EventBus and decouple modules
2025-11-22 deploy: 6e5cd937e38bc505492c90c54513485482eb6f2e
2025-11-22 Remov useless headers.
2025-11-22 Put config defines in config.c.
2025-11-22 deploy: 930f14e729aab3a1362d82ce15456d60285f1e3c
2025-11-22 deploy: e5c9c153fd2a2442871ba10e334b3ff2905254e3
2025-11-22 deploy: 3e331b62fb87eede5ded0e46216e2b39dc27398e
2025-11-23 Moving esp_stub.h to test directory. Moving clock_task and gpio_task to components directory.
2025-11-23 deploy: ddfd11a5e2533744a15109292f97be3ba4995c3f
2025-11-23 deploy: a19503ea835ad4f0e285a5d8a04018cd1ac528ec
2025-11-27 Remove circular dependency.
2025-11-27 deploy: a9d8adf45ba87471f9342c0e97c93991eec3c4e8
2025-11-28 Add a payload in the evt_bus module (to remove clockUpdateQueue).
2025-11-28 deploy: cadf63e1907b4636e0d7cc20e9a9b443aa028e79
2025-11-28 Remove clock_task.h dependency. Misra fix.
2025-11-28 deploy: e7a13bda3adc46914b2b3d8809124a5f04a3071d
2025-11-28 deploy: d1ca12668c63c82b3457c43f356c2e2331727c4d
2025-11-28 Remove buttonQueue.
2025-11-28 deploy: 4d3fac7da8d01c24ef52e004981cc56cf7871141
2025-11-28 deploy: bcad1f4a3e2003c06a41bee3ee703921acaf2372
2025-11-28 Add mutex to protect clock struct. Simplify struct in gpio_task to avoid cast.
2025-11-29 Put unsigned where it was missing.
2025-11-29 Lower internal system wdg. Add task wdg on main for testing.
2025-11-29 deploy: 9f3d02a0861413d883383ab4ae2f6a49050c41f3
2025-11-29 Remove useless prototype.
2025-11-29 Remove enum, to control their type.
2025-11-29 deploy: c681e61e18c18c95ab0357e69454dec0e7987e9d
2025-11-29 deploy: 5c3ed880eae2cd75c38ef356c010df58a6fa45db
2025-11-29 deploy: d5ad885624d7aa4272fd4a3b9ec1458c6db9dcfb
2025-12-01 Add task watchdogs.
2025-12-01 deploy: 2d94629a85e8a79f90b0e338fded55900d1dbf22
2025-12-01 Rename dispatcher to dispatcher_task.
2025-12-01 deploy: f1eb0ffc9584a37c9669fdcbc9e1125037d69ce9
2026-01-12 First start on real ESP-32 C3 hardware.
2026-01-12 deploy: a5e76d467ccbe6f4102a297ea6dbbb5a36c95fe0
2026-01-12 Fix time_sync_task that was not started because of watchdog issues.
2026-01-12 deploy: 74b546c6e4fc8a7e96d51cde5f96a69959b79497
2026-01-18 Wifi is only updated when its configuration changed. NTP sync is done every 30s for testing. Make Wifi STA check thread safe.
2026-01-18 deploy: 6a36bfeb7de5e2fd608250b89fc62696ca8ce014
2026-01-19 deploy: 63e0f457101133aac57ea385b6530c1e8e7958a8
2026-02-07 Enable rotary encoder. Add internal pullups.
2026-02-07 deploy: 829e2bd2793b4736f1151e3a58fab682d9ec6e3d
2026-02-07 deploy: 40d466778aaa27b208146074f69fe725676b1a6f
2026-02-07 deploy: c74c4261e63074f8295dfa0cb6c32f684b998de8
2026-02-07 deploy: 460db7f88c84c201526bcac37e559b44a0eedc6c
2026-02-08 deploy: b2e8b7d956561fb63ab88745f02ef83c7dfa2aac
2026-02-08 deploy: e237d7c757321a4bfc1720868e7a443e0217d88c
2026-02-08 deploy: 9d25e77f5829be5a3d4d6ad164bfe79ab3e599c9
2026-02-08 deploy: e464a5157ab49d753a012bdfeaa2b984c72a9149
2026-02-08 Update README.md. License change to LGPLv3.
2026-02-09 Rotary encoder with interrupts.
2026-02-10 Rotary encoder adjustement, read all the event queue Misra fix.
2026-02-10 deploy: 2b9e36ce2fc54533319d3e88a9abbe6efee1ec82
2026-02-10 deploy: d705992e13a237806d49e9e97e2ea5106e1d9867
2026-02-14 Fix uint8_t underflow for clock.c Fix missing overflow, input verification, incorrect variable in log.
2026-02-14 deploy: 69d9bf06dbb12dbd587aee7555f200a2cd8d9bca
2026-02-14 Reduce html_format variable scope.
2026-02-15 Remove undefined function.
2026-02-15 deploy: 7fa80020152730e6e0f776bba08f03002157eb1e
2026-02-15 Fix incorrect comment.
2026-02-15 Avoid initializing blanking pin in hv5622.c as it is configured in pwm.c
2026-02-15 deploy: 7fcc334d7e46fe185184405bdc26207d0f19b09f
2026-02-15 Brightness slider ID mismatch on web page.
2026-02-15 Rotary encoder was not publishing the event.
2026-02-15 Fix race conditions in gpio_task.c.
2026-02-15 deploy: 93b0b2031a7304d3fb4ffae7403f9729a7a77c64
2026-02-15 Fix _config_read() return value.
2026-02-15 deploy: eb5ede5209c182b99e233338c66118fd10188e6e
2026-02-15 Fix XSS from ssid and passphrase.
2026-02-15 deploy: c7da5a7a817979577f1c4defbedf80db8c782b5b
2026-02-15 When config page is loaded, update the brightness value cursor.
2026-02-15 Add PWM event so PWM is updated with the web interface.
2026-02-15 deploy: ebda1f5e67d337f63d529690a3674c971b5ad8eb
2026-02-15 Fixing rotary encoder.
2026-02-15 deploy: dc0cc415d63db0bb6de34f5c8117cc5d398eac26
2026-02-15 deploy: 5eea6279b4817551ae22220c5fd675099a961d6a
2026-02-15 Reverse rotary button direction.
2026-02-16 Fix possible deadlock with eventbus.
2026-02-16 deploy: 2b20b4a44d31cc10fa40978fcc0335ebb64cce8a
2026-02-16 deploy: 2188bfbc38461ff50a81fb67c7cd69dbd9e584f1
2026-02-16 deploy: 22c15157547a22df0398cbc1e04462fe2b8e03fb
2026-02-16 deploy: 599843edcc881d554b94696212c073d74a9cba4d
2026-02-19 deploy: b5bbcd0c7d86e96c9bd825fe6712a75d9b2e6c05
2026-02-22 Update rotary encoder tests.
2026-02-22 Fix shift function.
2026-02-22 deploy: da5e9aba3157dc4eb0a376d14b30dfca785f7b78
2026-02-22 Allow clock update from web setup.
2026-02-22 deploy: e54a9368e971c34470b3e0ecab8a0d358d61e0b9
2026-02-22 Add display leading zero feature
2026-02-22 Display current time in the web setup.
2026-02-22 deploy: e407b57cfde0ceb20dc105154ac84292724a2c2e
